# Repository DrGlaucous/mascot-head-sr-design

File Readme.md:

# Dynamic eye mascot Sr. Design

## Locations:
- All software is in the `Software` folder
- All 3D CAD is in the `CAD` folder
- All PCB schematics are in the `Schematic` folder

## Notes

Useful info links:
- Compute io board v3: https://www.raspberrypi.com/documentation/computers/compute-module.html#cmio
- 

Things we've checked out from lab:
- x2 micro USB cables (robert)
- x1 usb TTL adapter (ed)
- x1 mini usb cable (ed)
- x1 HDMI + DP cable (robert)
- x1 Rpi3 (luis)

How to play mp3 files through the CLI:
mpg123 gives the help menu
the -f flag controls loudness (x out of 32768)

Example:
mpg123 -f 8000 JumpingJackson.mp3

## Setup (from a stock system)

To use the built-in display+camera, copy the config files in the software folder into the boot partition (renaming them)

Software dependencies:
python3-opencv
python3-pyaudio
python3-pygame
python3-scipy
python3-picamera2

put the software.service file in:
`/etc/systemd/system/`

```
commands to start it:

sudo systemctl daemon-reload
sudo systemctl enable software.service
sudo systemctl start software.service

commands to control or restart it
sudo systemctl stop software.service
sudo systemctl restart software.service

systemctl status software.service
```

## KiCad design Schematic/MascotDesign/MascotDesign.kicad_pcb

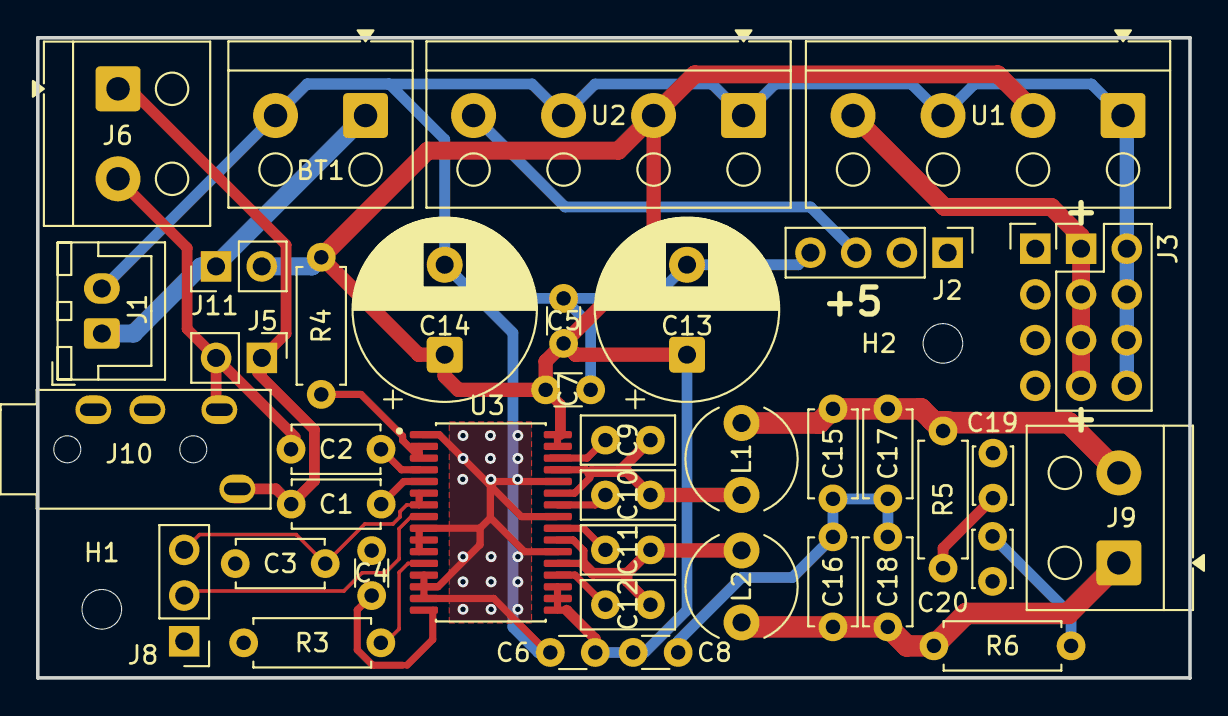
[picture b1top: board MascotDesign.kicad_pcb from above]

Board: 2 copper layers, 64.0 x 35.6 mm, 42 parts (0 on the bottom side), 24 nets.

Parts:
BT1: Battery and BMS; TerminalBlock_RND_205-00001_1x02_P5.00mm_Horizontal
C1, C2, C3, C15, C16, C17, C18: 1 uF; C_Disc_D4.7mm_W2.5mm_P5.00mm
C4, C5, C6: 1 nF; C_Disc_D3.0mm_W1.6mm_P2.50mm
C7, C8: 100 nF; C_Disc_D3.0mm_W1.6mm_P2.50mm
C9, C10, C11, C12: 220 nF; C_Disc_D5.0mm_W2.5mm_P2.50mm
C13, C14: 220 uF; CP_Radial_D10.0mm_P5.00mm
C19, C20: 10 nF; C_Disc_D3.0mm_W2.0mm_P2.50mm
H1, H2: MountingHole; MountingHole_2.2mm_M2
J1: Charger input; JST_XH_B2B-XH-A_1x02_P2.50mm_Vertical
J2: PI power USB; PinHeader_1x04_P2.54mm_Vertical
J3: LCD LED Power; PinHeader_2x04_P2.54mm_Vertical
J4: Dummy Header; PinHeader_1x04_P2.54mm_Vertical
J5: Audio in; PinHeader_1x02_P2.54mm_Vertical
J6: Audio in; TerminalBlock_RND_205-00001_1x02_P5.00mm_Horizontal
J8: Potentiometer; PinHeader_1x03_P2.54mm_Vertical
J9: Speaker 8R; TerminalBlock_RND_205-00001_1x02_P5.00mm_Horizontal
J10: AudioJack4; PJ-320A
J11: Main power cutoff (soldered switch); PinHeader_1x02_P2.54mm_Vertical
L1, L2: 10 uH; L_Radial_D6.0mm_P4.00mm
R3, R4: 100k; R_Axial_DIN0207_L6.3mm_D2.5mm_P7.62mm_Horizontal
R5, R6: 13.2 R; R_Axial_DIN0207_L6.3mm_D2.5mm_P7.62mm_Horizontal
U1, U2: Generic_Buck_Regulator; TerminalBlock_RND_205-00003_1x04_P5.00mm_Horizontal
U3: TPA3116D2DAD; SOP65P810X115-32N

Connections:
12V SWITCHED: C5.1, C6.1, C7.1, C8.1, C13.1, C14.1, J11.2, R4.1, U1.2 (IN), U2.2 (IN), U3.17 (AVCC), U3.18 (PVCC), U3.19 (PVCC), U3.31 (PVCC), U3.32 (PVCC)
+12V: BT1.1 (+), J1.1, J11.1
/Amplifier/Gain adjust supply: J8.2, U3.8 (GAIN/SLV)
/Amplifier/Power limit input: C3.2, J8.3, U3.6 (PLIMIT), U3.7 (GVDD)
/Power supply/PI 5v5: J2.3, U2.4 (OUT)
GND: BT1.2 (-), C3.1, C4.2, C5.2, C6.2, C7.2, C8.2, C13.2, C14.2, C15.1, C16.2, C17.1, C18.2, C19.1, C20.2, J1.2, J2.4, J3.2, J3.4, J3.6, J3.8, J8.1, R3.2, U1.1 (GND), U1.3 (GND), U2.1 (GND), U2.3 (GND), U3.1 (MODSEL), U3.9 (GND), U3.10 (LINP), U3.11 (LINN), U3.13 (AM2), U3.14 (AM1), U3.15 (AM0), U3.22 (GND), U3.25 (GND), U3.28 (GND)
LCD 5v5: J3.1, J3.3, J3.5, J3.7, U1.4 (OUT)
unnamed: C19.2, R5.2
unnamed: C20.1, R6.1
unnamed: C1.1, J5.1, J6.1, J10.S
unnamed: C2.2, J5.2, J6.2, J10.T
unnamed: C16.1, C18.1, J9.1, L2.1, R6.2
unnamed: C15.2, C17.2, J9.2, L1.1, R5.1
unnamed: C12.2, U3.20 (BSNL)
unnamed: C10.2, U3.26 (BSNR)
unnamed: C11.2, U3.24 (BSPL)
unnamed: C9.2, U3.30 (BSPR)
unnamed: R4.2, U3.2 (SDZ), U3.3 (FAULTZ)
unnamed: R3.1, U3.12 (MUTE)
unnamed: C11.1, C12.1, L2.2, U3.21 (OUTNL), U3.23 (OUTPL)
unnamed: C9.1, C10.1, L1.2, U3.27 (OUTNR), U3.29 (OUTPR)
unnamed: C1.2, U3.5 (RINN)
unnamed: C2.1, U3.4 (RINP)
unnamed: C4.1, U3.16 (SYNC)

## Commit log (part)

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2026-01-28 woohoo! first commit!
    add face reference from slide deck
2026-02-18 Begin work on schematic
    This uses kicad 9.0!
2026-02-18 Added display subsystem skeleton
2026-02-18 Edited display.py
2026-02-18 Work on schematic
    create power module and LED module in the master sheet
2026-02-18 organize PCB schematic into different files
    so multiple people can edit different parts
2026-02-18 Create a
2026-02-18 Unfinished audio schematic
2026-02-20 Effectively the amplifier circuit, compressed
2026-02-20 Tentative amplifier circuit
2026-02-25 Work on power supply schematic
2026-02-25 Work on initial CAD
    Also rename the old audio folder so we know it's not being used.
2026-02-26 display.py updated for demo on Friday
2026-02-27 oops. Misspelled reference folder
2026-02-27 fix some minor differences in amplifier circuit
2026-02-28 Initial audio demo - non-blocking loopback forever
2026-02-28 Basic filter - sounds weird IMO
2026-02-28 Integrate Butterworth filter into audio demo
    Added Butterworth filter to process audio input.
2026-02-28 Update PCB schematics folder reference in README
2026-03-03 Assign footprints and begin PCB layout
    Need to check the ECE shop to see what parts we have on hand before we get too far into this, but still.
    It's a start.
2026-03-04 Display.py changes for demo
2026-03-04 Added funny image
2026-03-05 Add soundcheck.py to play wave files
    This script plays a wave file using PyAudio.
2026-03-05 Add sample audio
    Only WAV file I had on-hand, somehow; not sure what it is
2026-03-06 Software Subsystem in rough state
2026-03-06 Work on CAD and schematics
    Got most of the components modeled for reference, now arranging them and creating brackets
2026-03-10 Do PCB layout
    I need to check our cap footprints to make sure we got the right ones.
    Other than that, the PCB should be mostly routed.
2026-03-10 update PCB and mounting brackets
    give PCB the correct footprints for the parts we have and add more mounting brackets for the 3D model
2026-03-10 ensure board passes DRC errors
    not warnings though. Those are mostly just silkscreen overlaps.
    We need to put something funny on the silkscreen yet.
2026-03-11 Tweak PCB and make power traces slightly thicker
    They should be plenty wide for our application, but if we have room, we may as well.
    I may go back and replace the speaker output traces with fill zones later to minimize impedance.
2026-03-12 Eye tracker source and demo code
    Import the EyeTracker class from the EyeTracker file to use it.
2026-03-13 Add pitch-shifting, calibration
2026-03-13 Adjust sample rate and filter initialization
    Updated sample rate to 48000 Hz, with a condition for x86_64 machines. Modified the filter initialization to include BUFFER_LENGTH.
2026-03-18 Add screen mounts to CAD and PCB silkscreen
2026-03-23 Slight PCB tweaking
2026-03-25 Finalize and order PCB
    Ordered through JLC, so formatting was exported to match that
2026-03-25 Work on cad and upload more dts files
    Added template dts and bin files from the pi tutorial for easy access since the originals are no longer being hosted on github
2026-03-27 Made the display accept a list of x,y gaze position
2026-03-27 Normalized input eye gaze position
2026-03-31 Add pi CM4 cad refrences
    Kicad, documentation, and 3d model (exported from kicad)
2026-04-01 Add utility script for frequency response
2026-04-03 Latest version of audiodemo, works on Pi
2026-04-03 Clean up input_callback by removing firstTime
    Removed unused firstTime variable and related print statements.
2026-04-03 Butterworth as demoed in class
2026-04-08 added working config files | added "stabilizedGaze" to eyeTracker
2026-04-10 Move image into sub-folder
2026-04-10 added local haar_filter file | added vector normalizing to tacker
2026-04-10 Work on more CAD and schematic deisgn
2026-04-10 Fixed an issue with eye-tracking not being able to find haarcascade_eye.xml
2026-04-14 Update PCB with correct TRRS pinout
    Also begin work on the actual pete mask CAD
2026-04-15 fixed ROI being set to None | wrapped audioDemmo in a function so it's not standalone
2026-04-17 Display split working
2026-04-17 Display: prevent stuff from crossing over
2026-04-17 Added png display capabilities to Display.py
2026-04-17 Added pete eyes
2026-04-17 removed deprecated dual_display
2026-04-24 Added modes to Purdue pete
2026-04-24 Fixed audio demo to use correct frequency range
2026-04-24 Display eyes made smaller
2026-04-24 Fixed butterworth filter blowing out audio
2026-04-24 Centered Pete eyes
2026-04-24 Creepy eye mode added
2026-04-28 add tweaked python files and system service file
    tweaked the python files to exit cleanly
    and set up a system service to handle starting and stopping the program
2026-04-28 Allow for other audio files to be tested
2026-04-28 Refactor audio into AudioManager object able to switch between filters
2026-04-28 Use refactored AudioManager in the GazeDisplay, and main file
2026-05-01 Work on CAD and export head + hat slices
